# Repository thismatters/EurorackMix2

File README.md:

# Mix

A simple mixing circuit which allows adjustment of each input before combining to a single output. Really simple.

The KiCAD project here uses the library/footprints [found in my companion repo](https://github.com/thismatters/EurorackKiCAD).

## Width

6hp

## Inputs

- Four signal jack
- Four signal knobs

## Outputs

One signal jack with combined output

## Vendors

There are part numbers in the [BOM](mix2.csv) for many of the parts (not for basic passives though) at the following vendors:

* [Mouser](https://www.mouser.com): Needs no introduction. Get your ICs from here (or [digikey](https://www.digikey.com)).
* [Tayda Electronics](https://www.taydaelectronics.com/): Good supplier for passive components; audio jacks, and potentiometers. Their audio jacks are slightly smaller than the thonkiconn from thonk.
* [Love My Switches](https://lovemyswitches.com/): Has [really good knobs](https://lovemyswitches.com/anodized-aluminum-knob-the-lo-fi-1-4-smooth-shaft-12-5mm-od/) to go on those potentiometers!
* [OSHPark](https://oshpark.com/): Fast and (relatively) cheap PCB manufacturer. Prototype run pending.

## Changelog

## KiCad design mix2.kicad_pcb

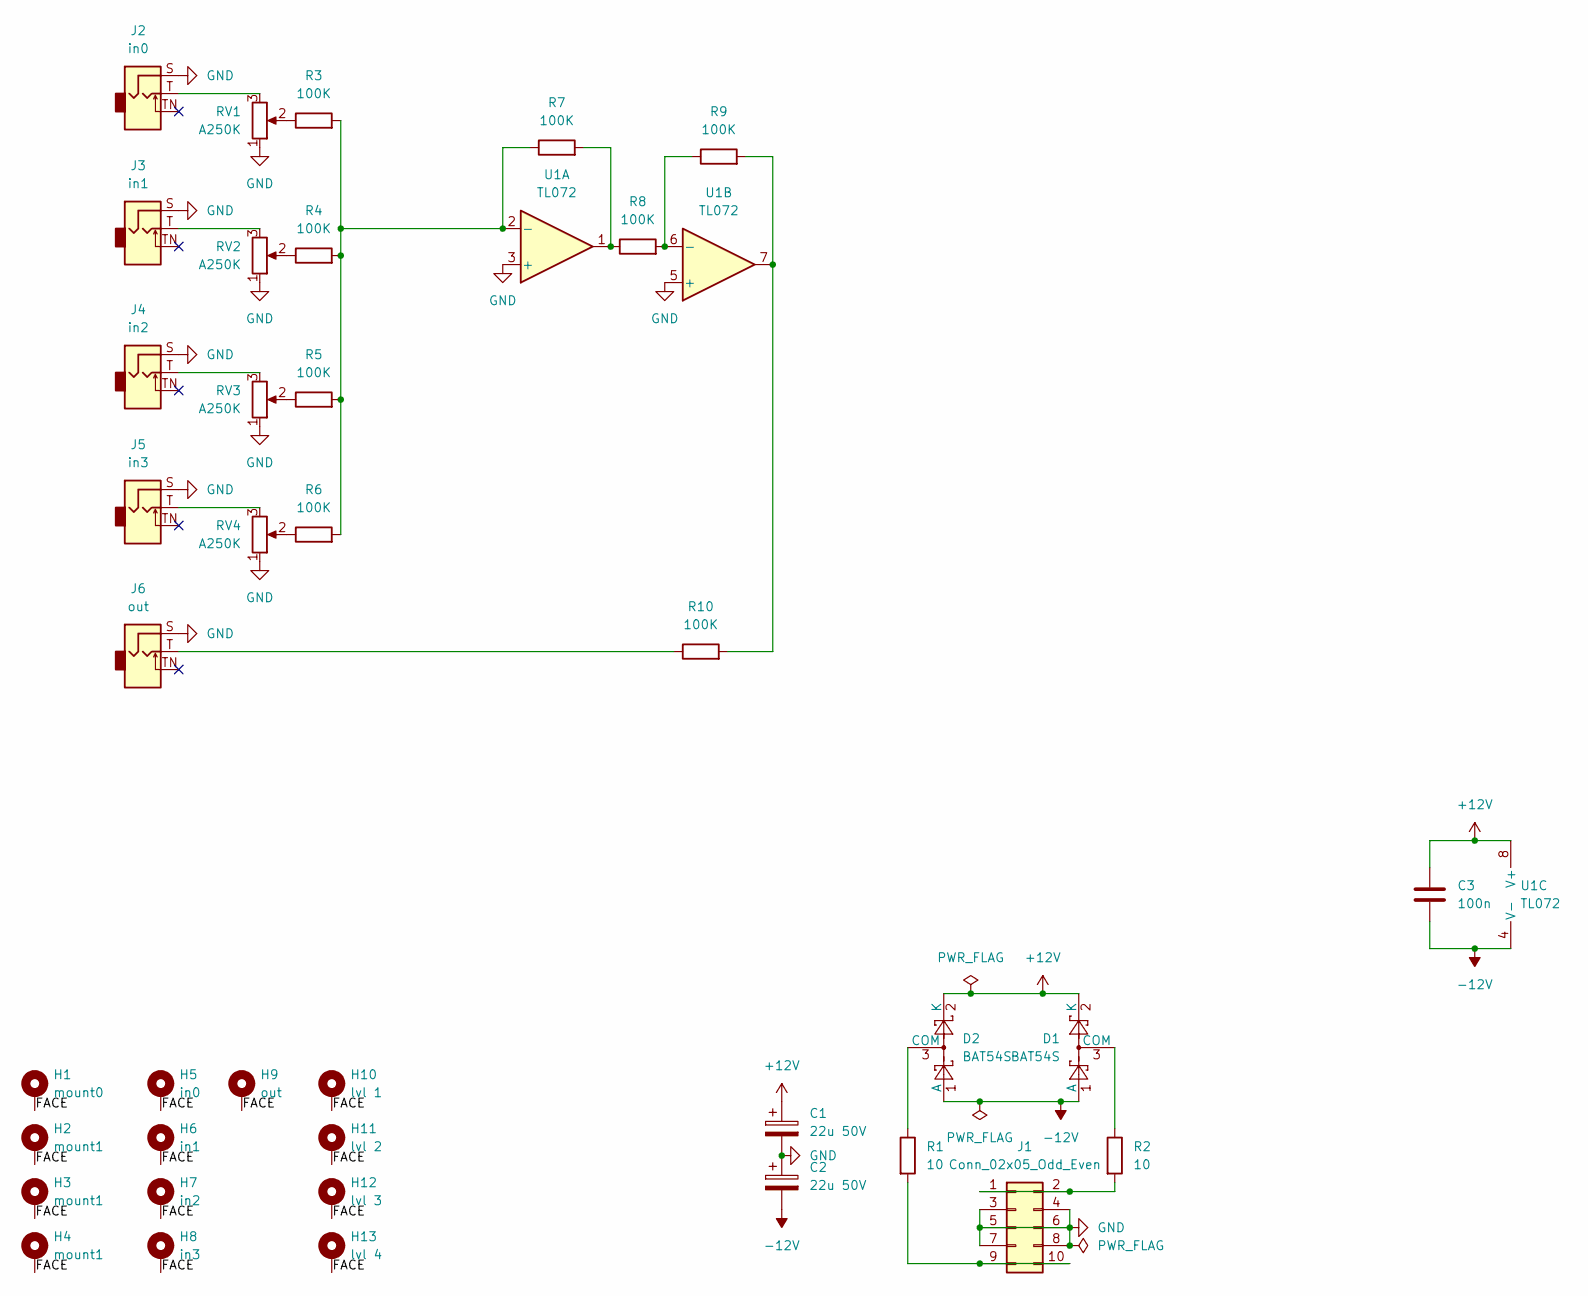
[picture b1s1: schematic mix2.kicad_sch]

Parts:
C1, C2: 22u 50V; CP_Radial_D5.0mm_P2.50mm
C3: 100n; C_0805_2012Metric
D1, D2: BAT54S; SOT-23; PartNum 863-BAT54SLT1G
H1: mount0; Mech-MountingHole
H2, H3, H4: mount1; Mech-MountingHole
H5: in0; Mech-AudioJack-Hole-Input
H6: in1; Mech-AudioJack-Hole-Input
H7: in2; Mech-AudioJack-Hole-Input
H8: in3; Mech-AudioJack-Hole-Input
H9: out; Mech-AudioJack-Hole-Output
H10: lvl 1; Mech-Potentiometer-Hole_level
H11: lvl 2; Mech-Potentiometer-Hole_level
H12: lvl 3; Mech-Potentiometer-Hole_level
H13: lvl 4; Mech-Potentiometer-Hole_level
J1: Conn_02x05_Odd_Even; PinHeader_2x05_P2.54mm_Vertical; PartNum A-2939
J2: in0; AudioJack2_Tayda_A-2566; PartNum A-2566
J3: in1; AudioJack2_Tayda_A-2566; PartNum A-2566
J4: in2; AudioJack2_Tayda_A-2566; PartNum A-2566
J5: in3; AudioJack2_Tayda_A-2566; PartNum A-2566
J6: out; AudioJack2_Tayda_A-2566; PartNum A-2566
R1, R2: 10; R_0805_2012Metric
R3, R4, R5, R6, R7, R8, R9, R10: 100K; R_0805_2012Metric
RV1, RV2, RV3, RV4: A250K; Potentiometer_RV16AF-41-15R1
U1: TL072; SOIC-8_3.9x4.9mm_P1.27mm; PartNum 595-TL072CDR

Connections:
+12V: C1.1, C3.1, D1.2 (K), D2.2 (K), U1.8 (V+)
-12V: C2.2, C3.2, D1.1 (A), D2.1 (A), U1.4 (V-)
/FACE: H1.1 (1_1), H2.1 (1_1), H3.1 (1_1), H4.1 (1_1), H5.1 (1_1), H6.1 (1_1), H7.1 (1_1), H8.1 (1_1), H9.1 (1_1), H10.1 (1_1), H11.1 (1_1), H12.1 (1_1), H13.1 (1_1)
GND: C1.2, C2.1, J1.3, J1.4, J1.5, J1.6, J1.7, J1.8, J2.S, J3.S, J4.S, J5.S, J6.S, RV1.1, RV2.1, RV3.1, RV4.1, U1.3 (+), U1.5 (+)
unnamed: D1.3 (COM), R2.1
unnamed: D2.3 (COM), R1.1
unnamed: J1.1, J1.2, R2.2
unnamed: J1.9, J1.10, R1.2
unnamed: J2.T, RV1.3
unnamed: J3.T, RV2.3
unnamed: J4.T, RV3.3
unnamed: J5.T, RV4.3
unnamed: J6.T, R10.1
unnamed: R3.1, RV1.2
unnamed: R4.1, RV2.2
unnamed: R5.1, RV3.2
unnamed: R6.1, RV4.2
unnamed: R7.2, R8.1, U1.1
unnamed: R9.2, R10.2, U1.7
unnamed: R3.2, R4.2, R5.2, R6.2, R7.1, U1.2 (-)
unnamed: R8.2, R9.1, U1.6 (-)

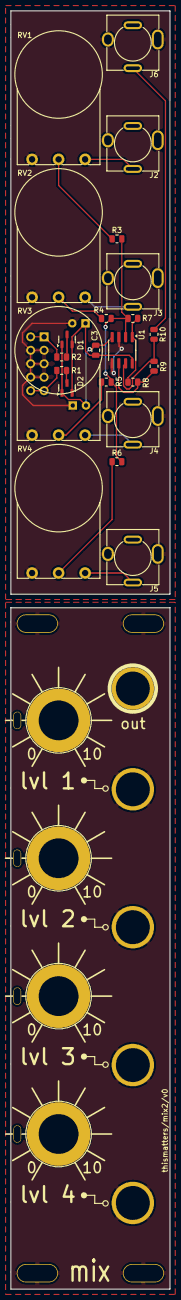
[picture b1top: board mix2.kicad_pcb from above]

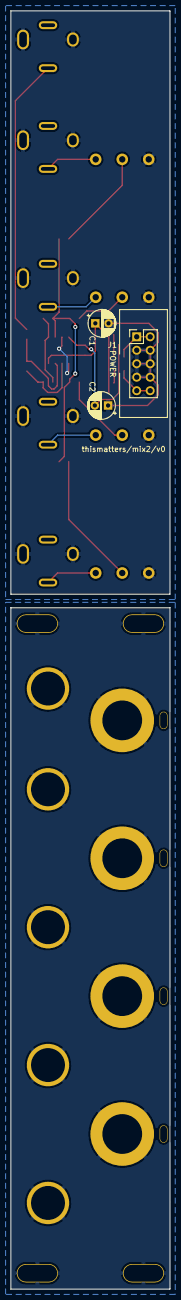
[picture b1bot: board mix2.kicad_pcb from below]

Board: 2 copper layers, 30.0 x 241.0 mm, 39 parts (3 on the bottom side), 21 nets.

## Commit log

2026-04-30 add schematic
2026-05-03 add bom
2026-05-03 fix bom issues
2026-06-06 fix alignment for manu
